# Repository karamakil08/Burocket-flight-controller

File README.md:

# Burocket Flight Controller

This is a flight controller built around the STM32F405 MCU for model rocket applications designed to perform altitude, gyro, and acceleration measurements, fire pyrotechnics, and save flight data safely.

## Component Selection

The components selected for this project were chosen according to various measures:
* Application requirement
* Ease of supply
* Price
* Performance
* Footprint area

## Hardware Subsystems

Detailed documentation for each subsystem can be found below:

* [MCU](docs/MCU.md)
* [Sensors](docs/Sensors.md)
* [POWER](docs/POWER.md)
* [Relays](docs/Relays.md)
* [LoRa](docs/LoRa.md)
* [USB-C](docs/USB-C.md)
* [Flash Memory](docs/Flash_memory.md)
* [SD-Card](docs/SD-card.md)

## Pin Distribution & Firmware

You can find the STMCubeMX pin distribution and firmware source files here:
* 🔗 [Firmware Directory](https://github.com/karamakil08/Burocket-flight-controller/tree/main/Firmware)

## Documentation & Resources

* 🔗 [Datasheets](https://github.com/karamakil08/Burocket-flight-controller/tree/main/docs/Datasheets)
* 🔗 [Application Notes](https://github.com/karamakil08/Burocket-flight-controller/tree/main/docs/App%20notes)
* 🔗 [Additional Useful Resources](https://github.com/karamakil08/Burocket-flight-controller/blob/main/docs/App%20notes/Links%20to%20additional%20resources%20I%20found%20useful.md)

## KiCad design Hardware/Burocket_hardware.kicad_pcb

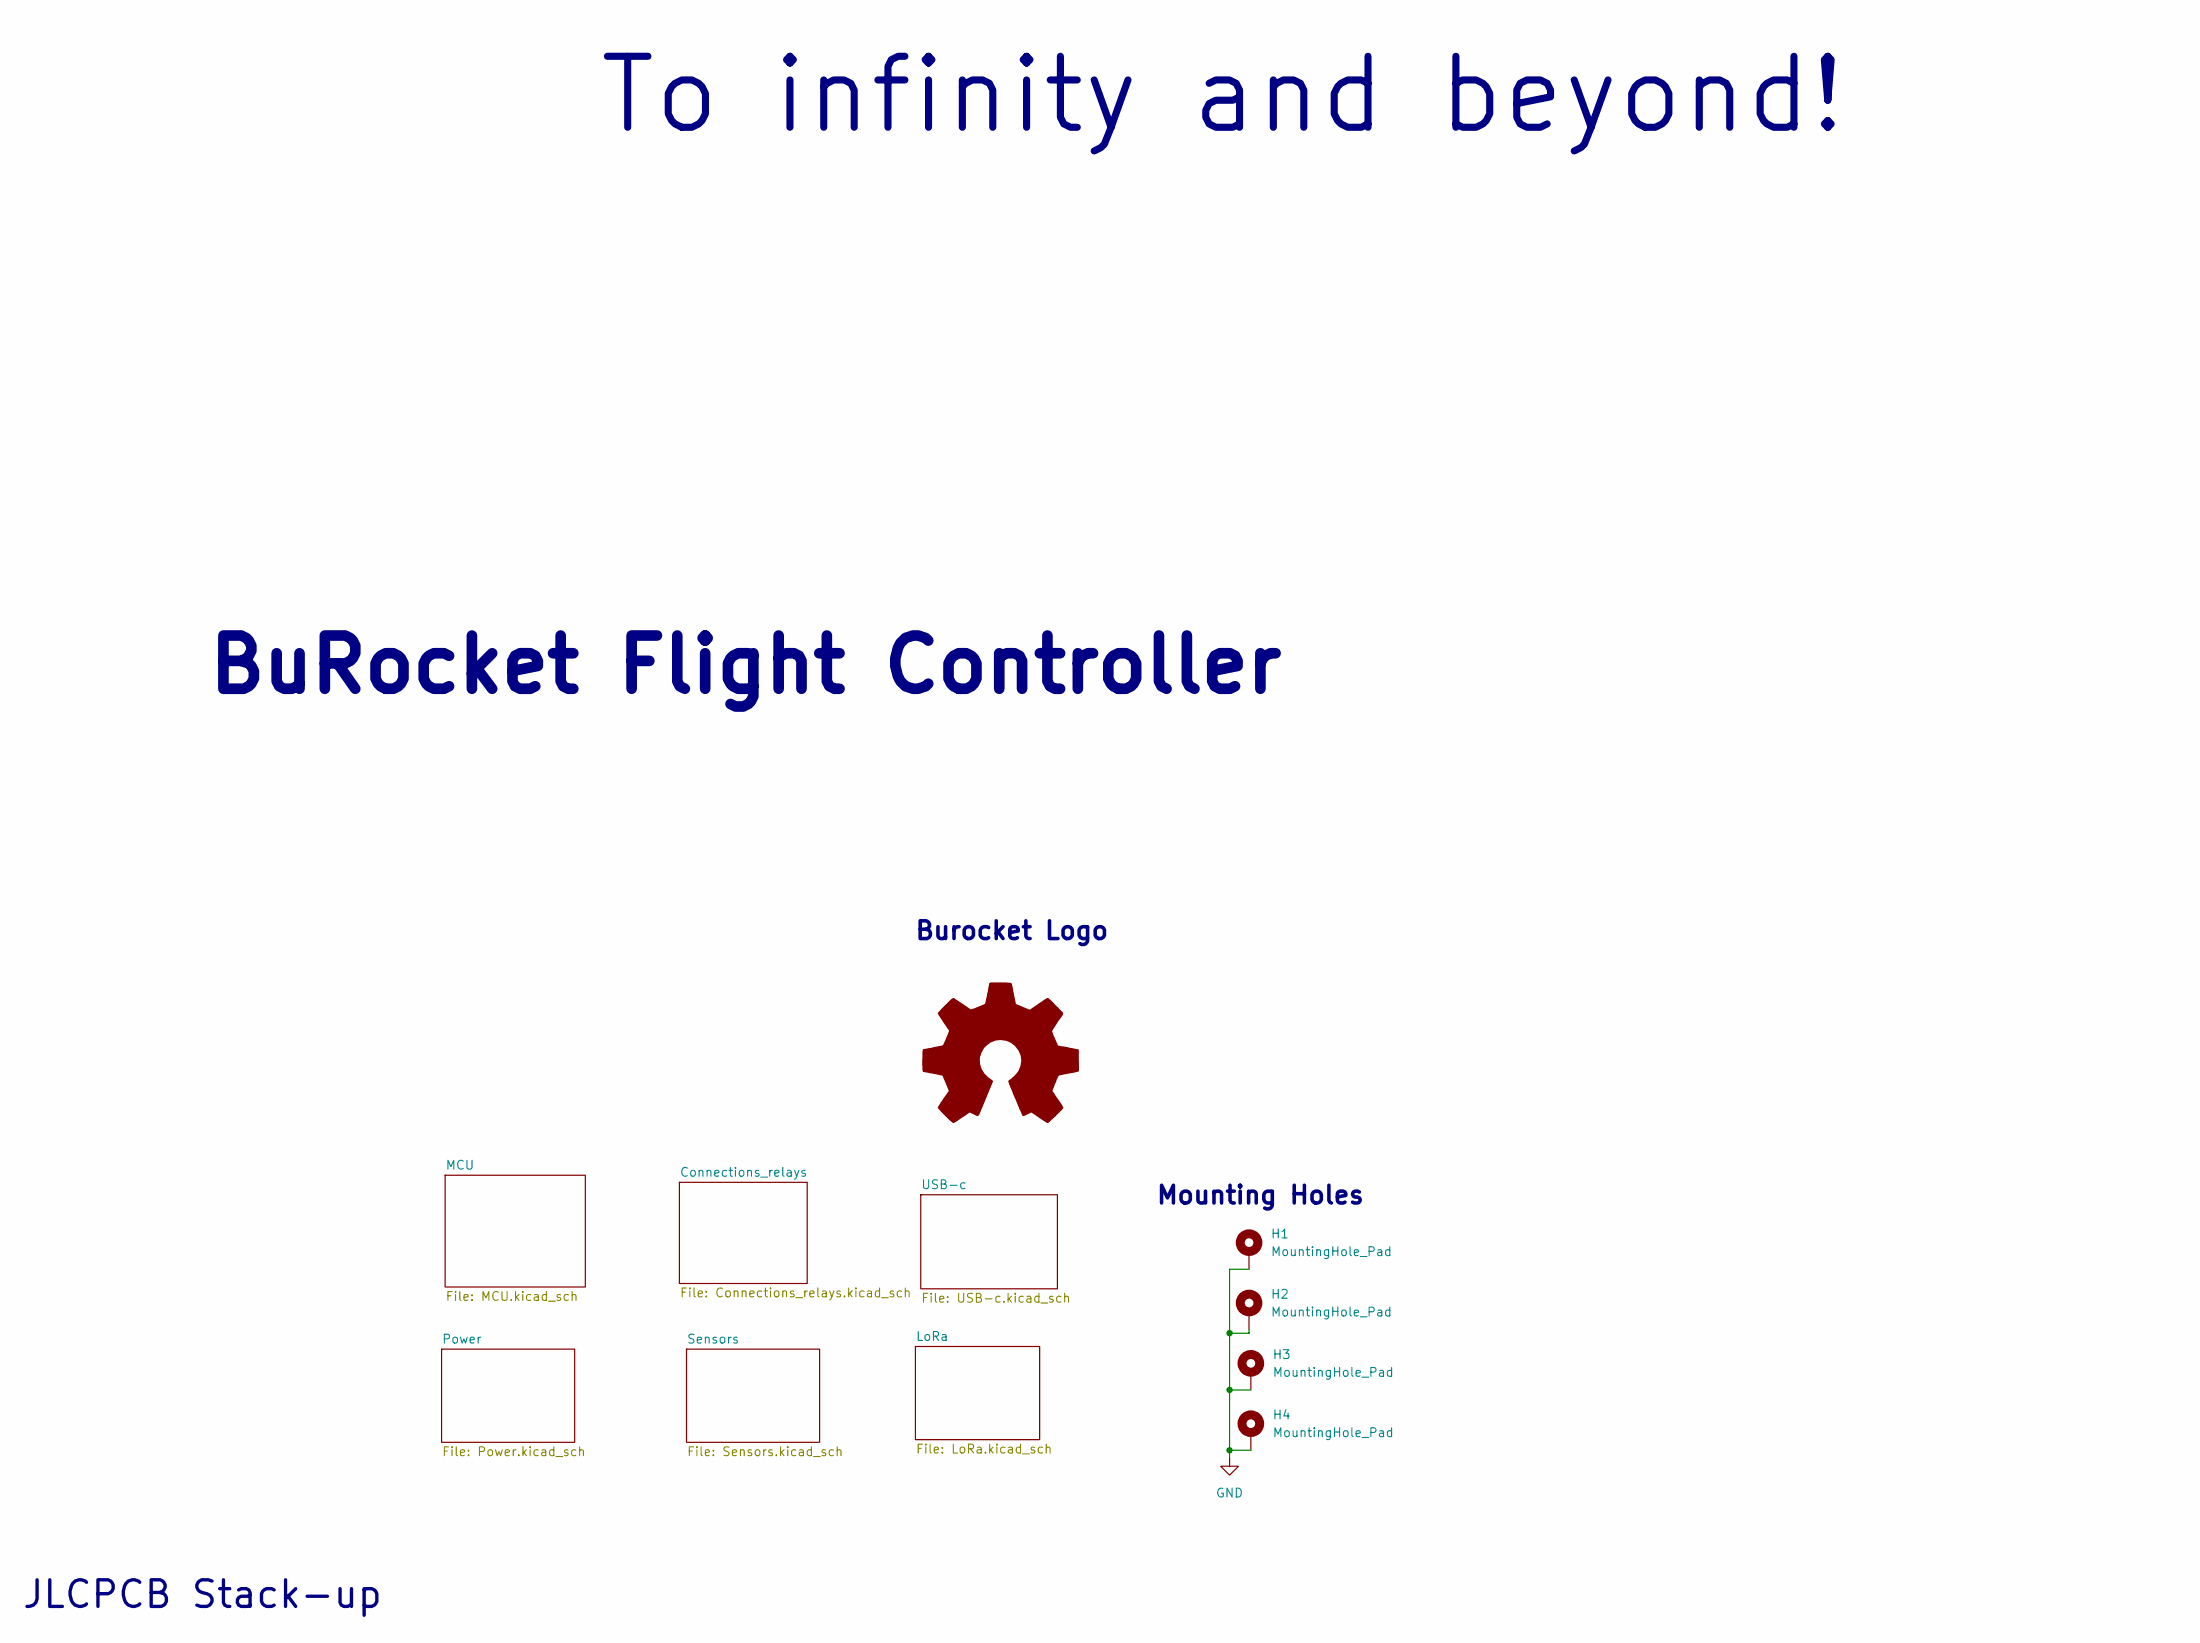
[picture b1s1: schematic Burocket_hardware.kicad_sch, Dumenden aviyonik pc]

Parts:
H1, H2, H3, H4: MountingHole_Pad; MountingHole_2.2mm_M2_Pad_Via
Logo1: Burocket Logo

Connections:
GND: H1.1 (1_1), H2.1 (1_1), H3.1 (1_1), H4.1 (1_1); also elsewhere on the board

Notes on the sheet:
Burocket Logo
BuRocket Flight Controller
JLCPCB Stack-up
Mounting Holes
To infinity and beyond!

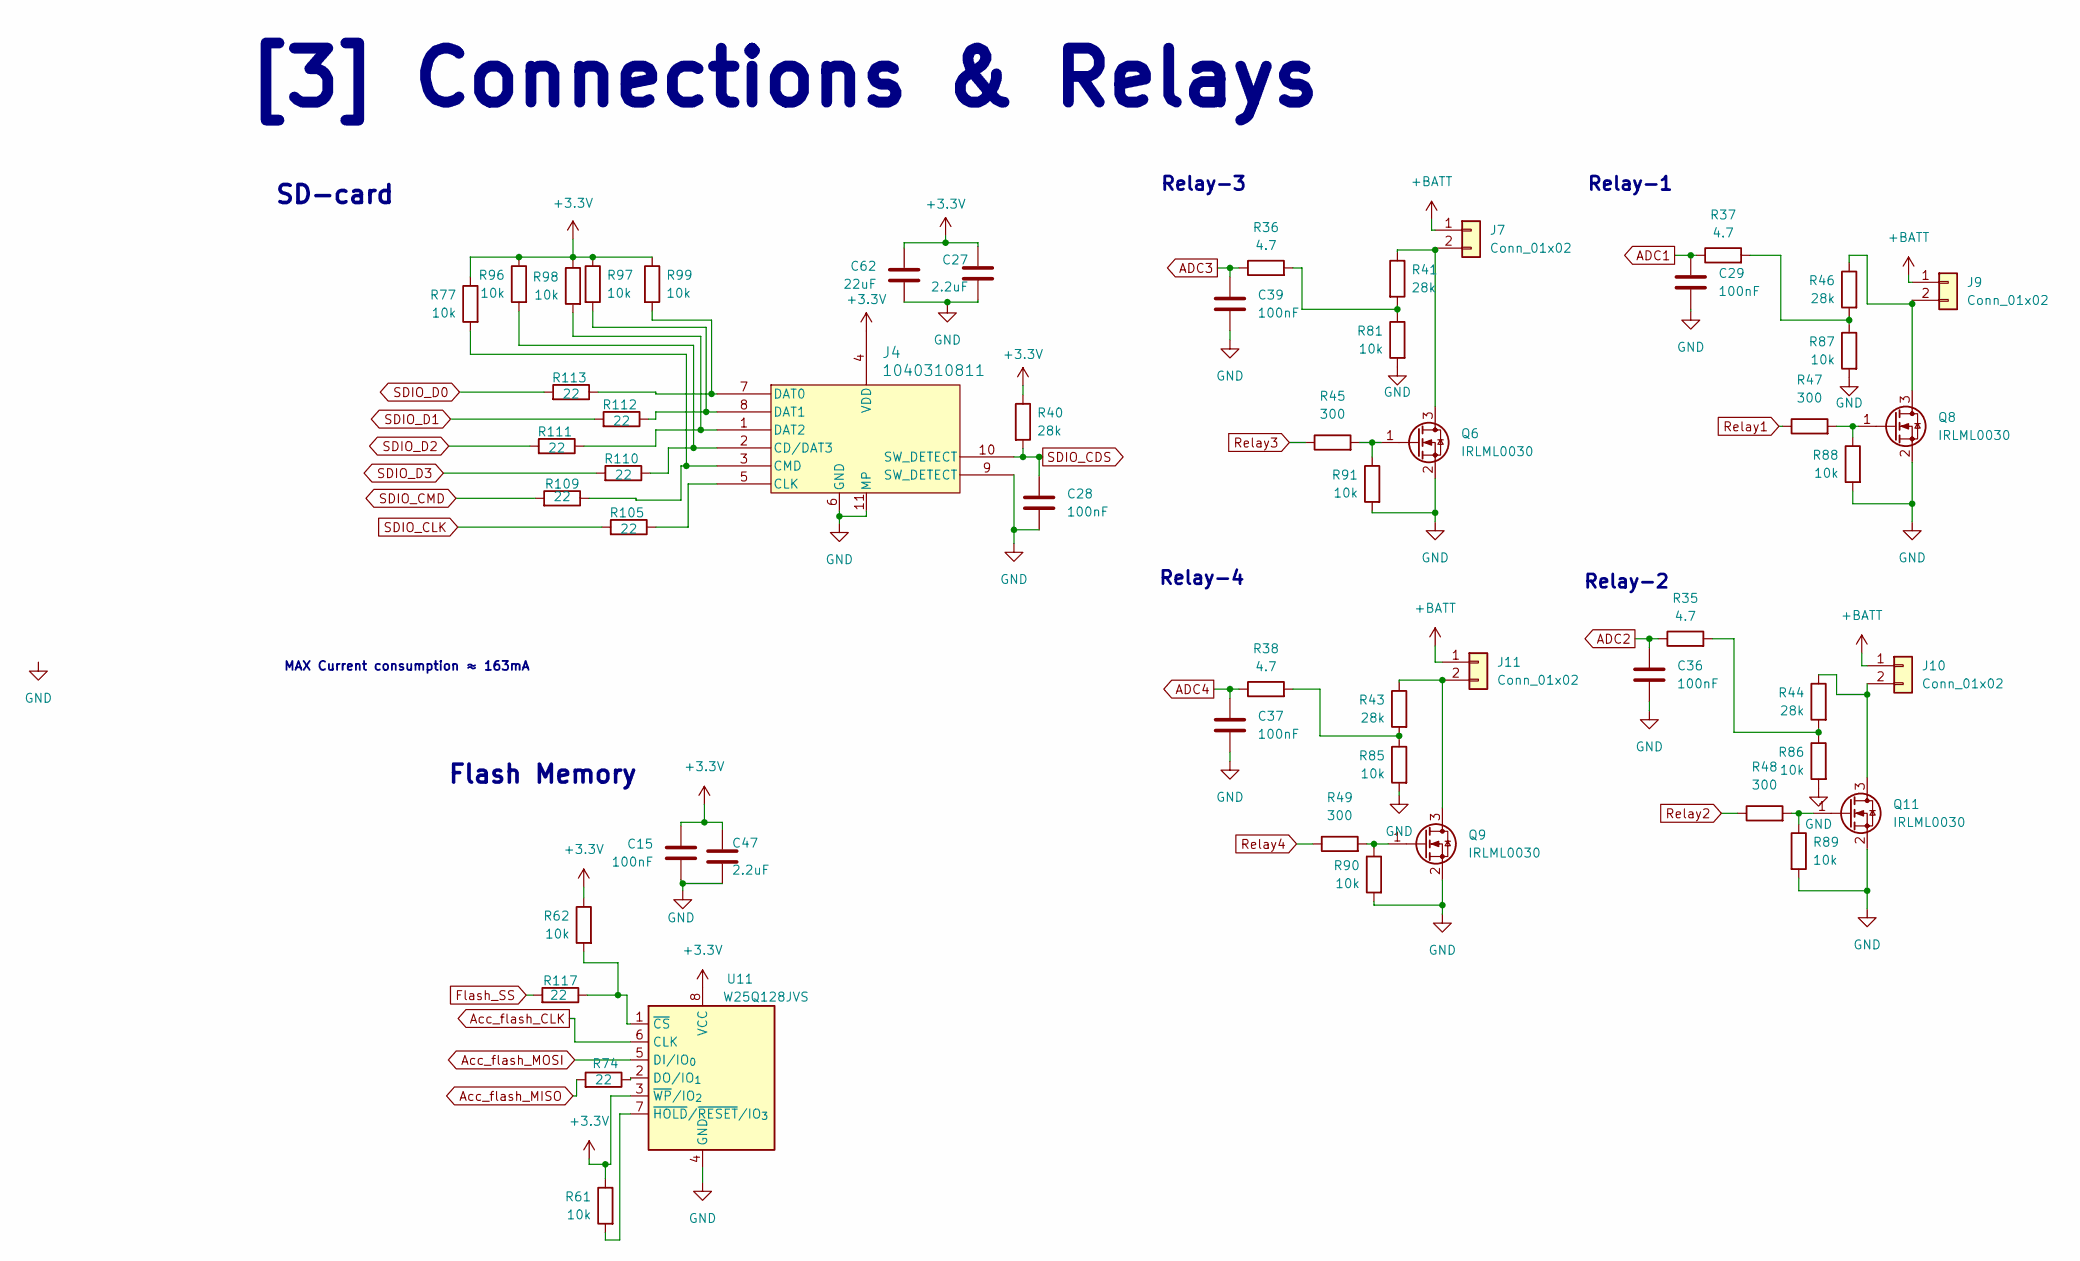
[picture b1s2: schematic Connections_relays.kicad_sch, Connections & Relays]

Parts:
C15, C28, C29, C36, C37, C39: 100nF; C_0603_1608Metric; Part Number CL10B104KO8WPNC
C27, C47: 2.2uF; C_0603_1608Metric; Part Number CL10B225KP8NNNC
C62: 22uF; C_0805_2012Metric; Part Number CL21A226KOQNNNE
J4: 1040310811; 104031-0811_MOL
J7, J9, J10, J11: Conn_01x02; E-match_Solder
Q6, Q8, Q9, Q11: IRLML0030; SOT-23
R35, R36, R37, R38: 4.7; R_0603_1608Metric; Part Number CQ03SAF470KT5E
R40, R41, R43, R44, R46: 28k; R_0603_1608Metric; Part Number MCT06030C2802FP500
R45, R47, R48, R49: 300; R_0603_1608Metric; Part Number ERJ3EKF3000V
R61, R62, R77, R88, R89, R90, R91, R96, R97, R98, R99: 10k; R_0603_1608Metric; Part Number CRT03J7E1002
R74, R105, R109, R110, R111, R112, R113, R117: 22; R_0603_1608Metric; Part Number CQ03SAJ0220T5E
R81, R85, R86, R87: 10k; R_0603_1608Metric; Part Number TC0350B1002T5F
U11: W25Q128JVS; SOIC-8_5.3x5.3mm_P1.27mm; Part Number W25Q128JVSIQ

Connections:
+3.3V: C15.1, C27.1, C47.1, C62.1, J4.4 (VDD), R40.1, R61.1, R62.1, R77.1, R96.1, R97.1, R98.1, R99.1, U11.3 (~WP/IO_{2}), U11.8 (VCC); also elsewhere on the board
+BATT: J7.1, J9.1, J10.1, J11.1; also elsewhere on the board
ADC1: C29.1, R37.1; also elsewhere on the board
ADC2: C36.1, R35.1; also elsewhere on the board
ADC3: C39.1, R36.1; also elsewhere on the board
ADC4: C37.1, R38.1; also elsewhere on the board
Acc_flash_CLK: U11.6 (CLK); also elsewhere on the board
Acc_flash_MOSI: U11.5 (DI/IO_{0}); also elsewhere on the board
Flash_SS: R117.2; also elsewhere on the board
GND: C15.2, C27.2, C28.2, C29.2, C36.2, C37.2, C39.2, C47.2, C62.2, J4.6 (GND), J4.9 (SW_DETECT), J4.11 (MP), J4.12 (MP), J4.13 (MP), J4.14 (MP), Q6.2 (S), Q8.2 (S), Q9.2 (S), Q11.2 (S), R81.2, R85.2, R86.2, R87.2, R88.2, R89.2, R90.2, R91.2, U11.4 (GND); also elsewhere on the board
unnamed: J4.2 (CD/DAT3), R96.2, R110.1
unnamed: J4.5 (CLK), R105.1
unnamed: J4.3 (CMD), R77.2, R109.1
unnamed: J4.7 (DAT0), R99.2, R113.1
unnamed: J4.8 (DAT1), R97.2, R112.1
unnamed: J4.1 (DAT2), R98.2, R111.1
unnamed: J7.2, Q6.3 (D), R41.1
unnamed: J9.2, Q8.3 (D), R46.1
unnamed: J10.2, Q11.3 (D), R44.1
unnamed: J11.2, Q9.3 (D), R43.1
unnamed: Q6.1 (G), R45.2, R91.1
unnamed: Q8.1 (G), R47.2, R88.1
unnamed: Q9.1 (G), R49.2, R90.1
unnamed: Q11.1 (G), R48.2, R89.1
unnamed: R35.2, R44.2, R86.1
unnamed: R36.2, R41.2, R81.1
unnamed: R37.2, R46.2, R87.1
unnamed: R38.2, R43.2, R85.1
unnamed: R74.1, U11.2 (DO/IO_{1})
unnamed: R62.2, R117.1, U11.1 (~CS)
unnamed: R61.2, U11.7 (~HOLD/~RESET/IO_{3})
Relay1: R47.1; also elsewhere on the board
Relay2: R48.1; also elsewhere on the board
Relay3: R45.1; also elsewhere on the board
Relay4: R49.1; also elsewhere on the board
SDIO_CDS: C28.1, J4.10 (SW_DETECT), R40.2; also elsewhere on the board
SDIO_CLK: R105.2; also elsewhere on the board
SDIO_CMD: R109.2; also elsewhere on the board
SDIO_D0: R113.2; also elsewhere on the board
SDIO_D1: R112.2; also elsewhere on the board
SDIO_D2: R111.2; also elsewhere on the board
SDIO_D3: R110.2; also elsewhere on the board

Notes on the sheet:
Relay-1
[3] Connections & Relays
Relay-3
MAX Current consumption ≈ 163mA
Flash Memory
Relay-4
SD-card
Relay-2

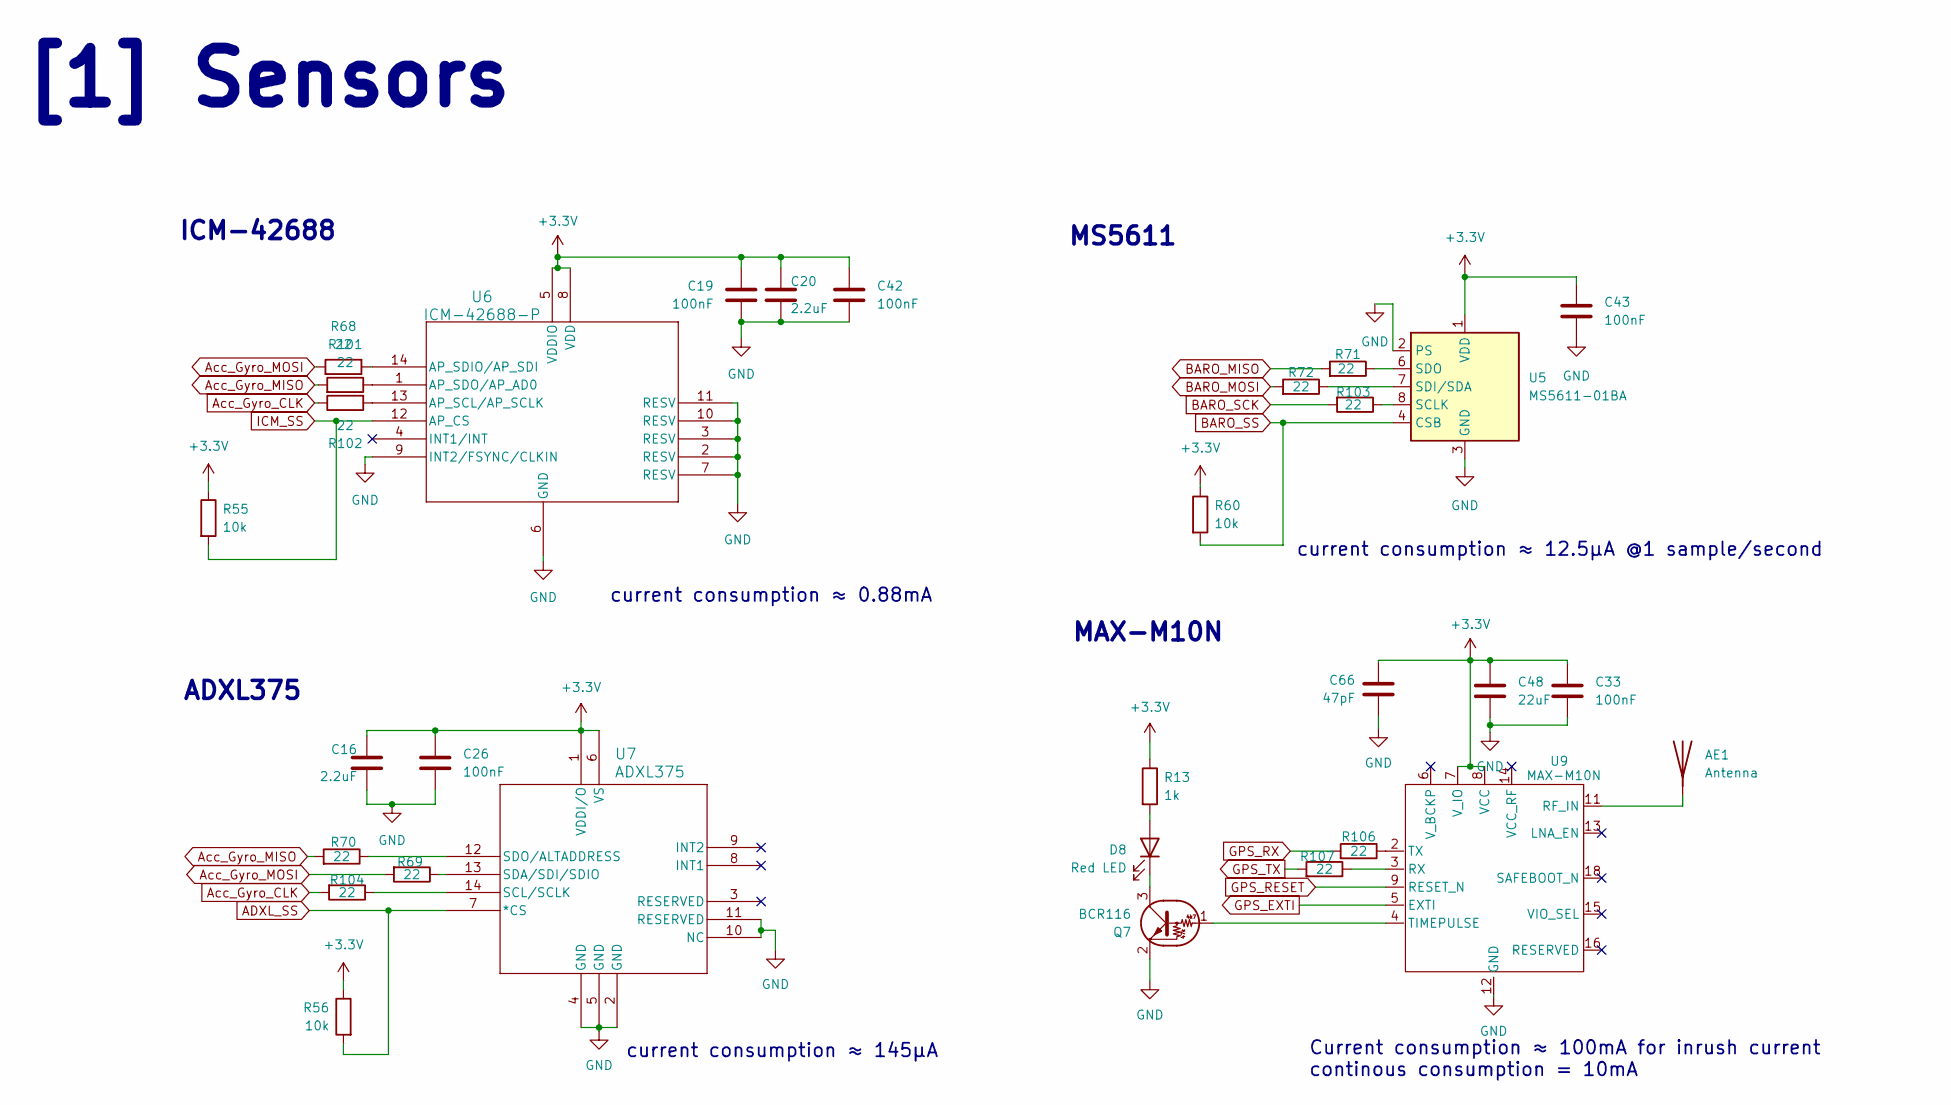
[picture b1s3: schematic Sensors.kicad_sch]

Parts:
AE1: Antenna; SMA_Amphenol_132134-10_Vertical
C16, C20: 2.2uF; C_0603_1608Metric; Part Number CL10B225KP8NNNC
C19, C26, C33, C42, C43: 100nF; C_0603_1608Metric; Part Number CL10B104KO8WPNC
C48: 22uF; C_0805_2012Metric; Part Number CL21A226KOQNNNE
C66: 47pF; C_0603_1608Metric; Part Number CL10C470JB81PNC
D8: Red LED; C_0603_1608Metric; Part Number 27-21/R6C-AP1Q2B/3C
Q7: BCR116; SOT-23-3; Part Number BCR116E6327HTSA1
R13: 1k; R_0603_1608Metric; Part Number CRCW06031K00JNTABC
R55, R56, R60: 10k; R_0603_1608Metric; Part Number CRT03J7E1002
R68, R69, R70, R71, R72, R101, R102, R103, R104, R106, R107: 22; R_0603_1608Metric; Part Number CQ03SAJ0220T5E
U5: MS5611-01BA; LGA-8_3x5mm_P1.25mm; Part Number MS561101BA03-50
U6: ICM-42688-P; LGA14_2P5X3X0P91_TDK; Part Number ICM-42688-P
U7: ADXL375; LGA_CC-14-1_ADI-L; Part Number ADXL375BCCZ-RL7
U9: MAX-M10N; ublox_MAX; Part Number MAX-M10N-00B

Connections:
+3.3V: C16.1, C19.1, C20.1, C26.1, C33.1, C42.1, C43.1, C48.1, C66.1, R13.1, R55.1, R56.1, R60.1, U5.1 (VDD), U6.5 (VDDIO), U6.8 (VDD), U7.1 (VDDI/O), U7.6 (VS), U9.7 (V_IO), U9.8 (VCC); also elsewhere on the board
/Sensors/Connector_feed: AE1.1, U9.11 (RF_IN); also elsewhere on the board
Acc_flash_CLK: R104.1, U7.14 (SCL/SCLK); also elsewhere on the board
Acc_flash_MOSI: R69.1, U7.13 (SDA/SDI/SDIO); also elsewhere on the board
BARO_icm_MOSI: R68.1, R72.1, U5.7 (SDI/SDA), U6.14 (AP_SDIO/AP_SDI); also elsewhere on the board
GND: C16.2, C19.2, C20.2, C26.2, C33.2, C42.2, C43.2, C48.2, C66.2, Q7.2 (E), U5.2 (PS), U5.3 (GND), U6.2 (RESV), U6.3 (RESV), U6.6 (GND), U6.7 (RESV), U6.9 (INT2/FSYNC/CLKIN), U6.10 (RESV), U6.11 (RESV), U7.2 (GND), U7.4 (GND), U7.5 (GND), U7.10 (NC), U7.11 (RESERVED), U9.1 (GND), U9.10 (GND), U9.12 (GND); also elsewhere on the board
GPS_RX: R106.2; also elsewhere on the board
GPS_TX: R107.2; also elsewhere on the board
unnamed: D8.2 (A), R13.2
unnamed: D8.1 (K), Q7.3 (C)
unnamed: Q7.1 (B), U9.4 (TIMEPULSE)
unnamed: R68.2, R69.2
unnamed 78: R60.2, U5.4 (CSB), U5.5 (CSB); also elsewhere on the board
unnamed: R71.1, U5.6 (SDO)
unnamed: R101.1, U6.1 (AP_SDO/AP_AD0)
unnamed 86: R56.2, U7.7 (*CS); also elsewhere on the board
unnamed: R70.1, U7.12 (SDO/ALTADDRESS)
unnamed 93: U9.5 (EXTI); also elsewhere on the board
unnamed 94: U9.9 (RESET_N); also elsewhere on the board
unnamed: R107.1, U9.3 (RX)
unnamed: R106.1, U9.2 (TX)

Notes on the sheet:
current consumption ≈ 12.5µA @1 sample/second
ICM-42688
[1] Sensors
MAX-M10N
current consumption ≈ 145µA
current consumption ≈ 0.88mA
MS5611
Current consumption ≈ 100mA for inrush current continous consumption = 10mA
ADXL375

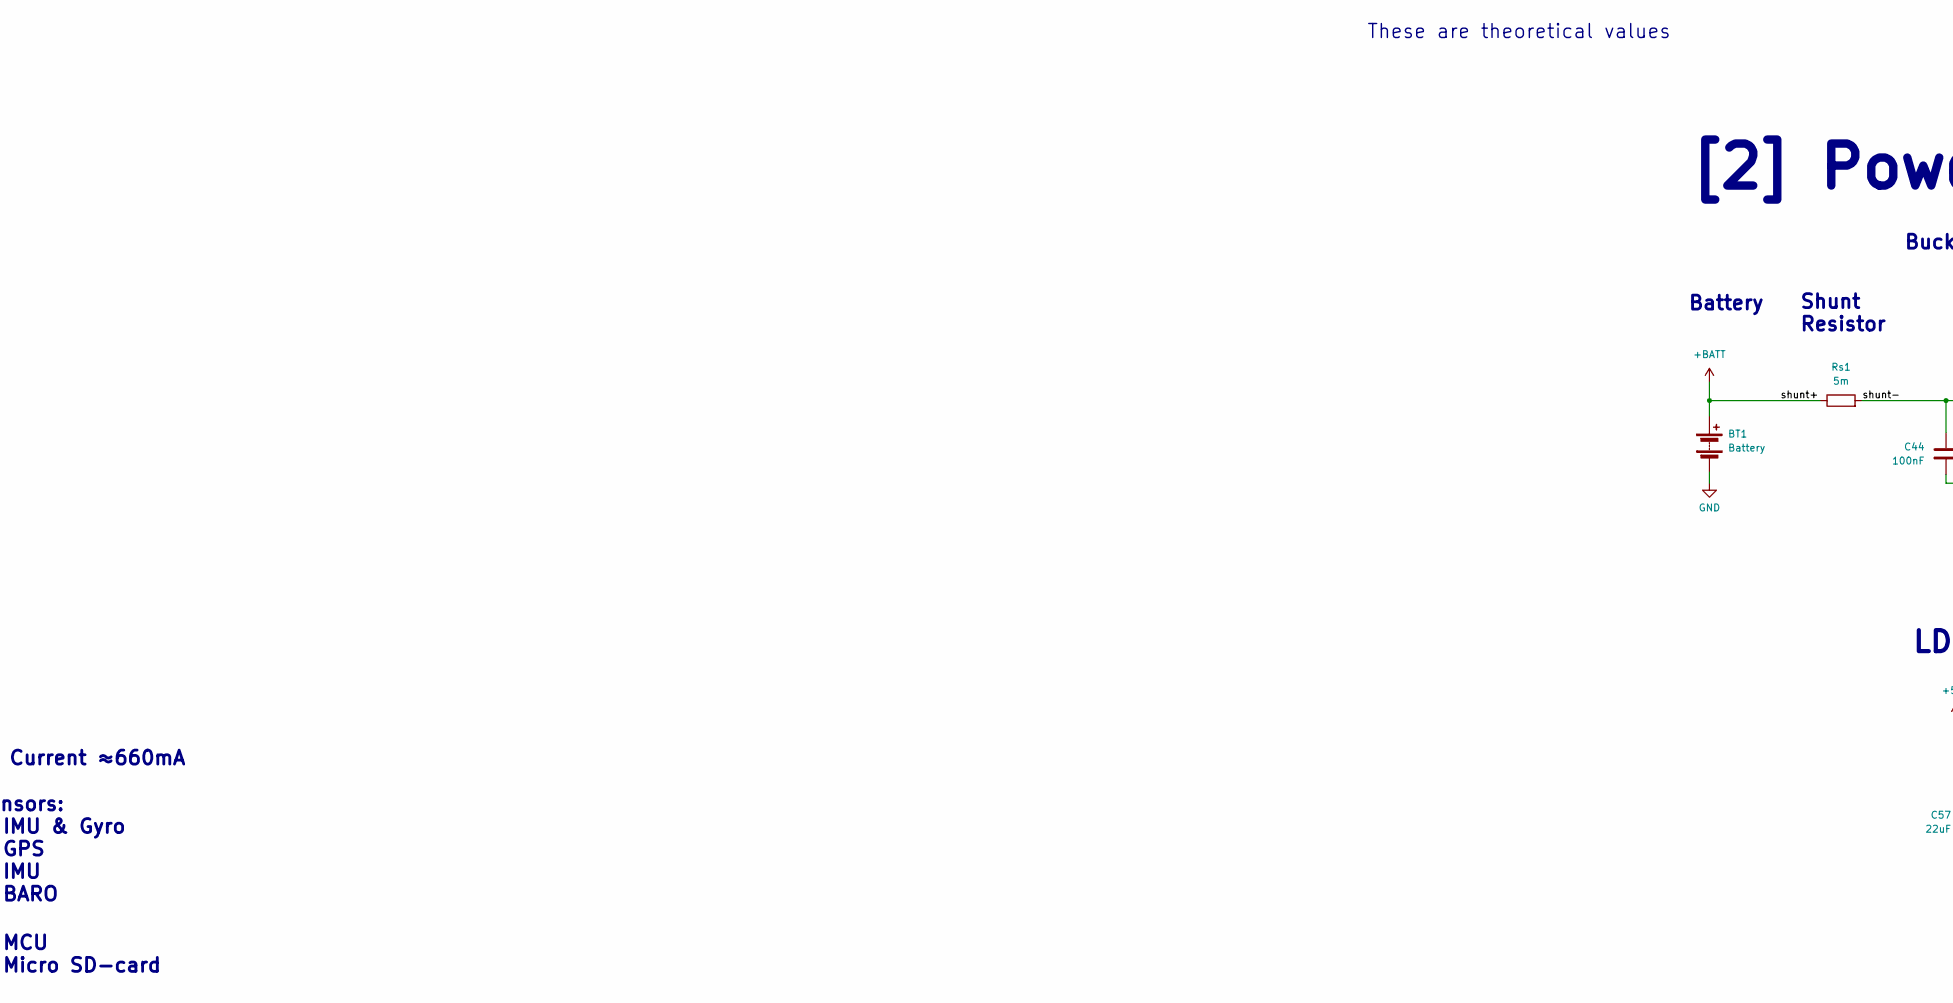
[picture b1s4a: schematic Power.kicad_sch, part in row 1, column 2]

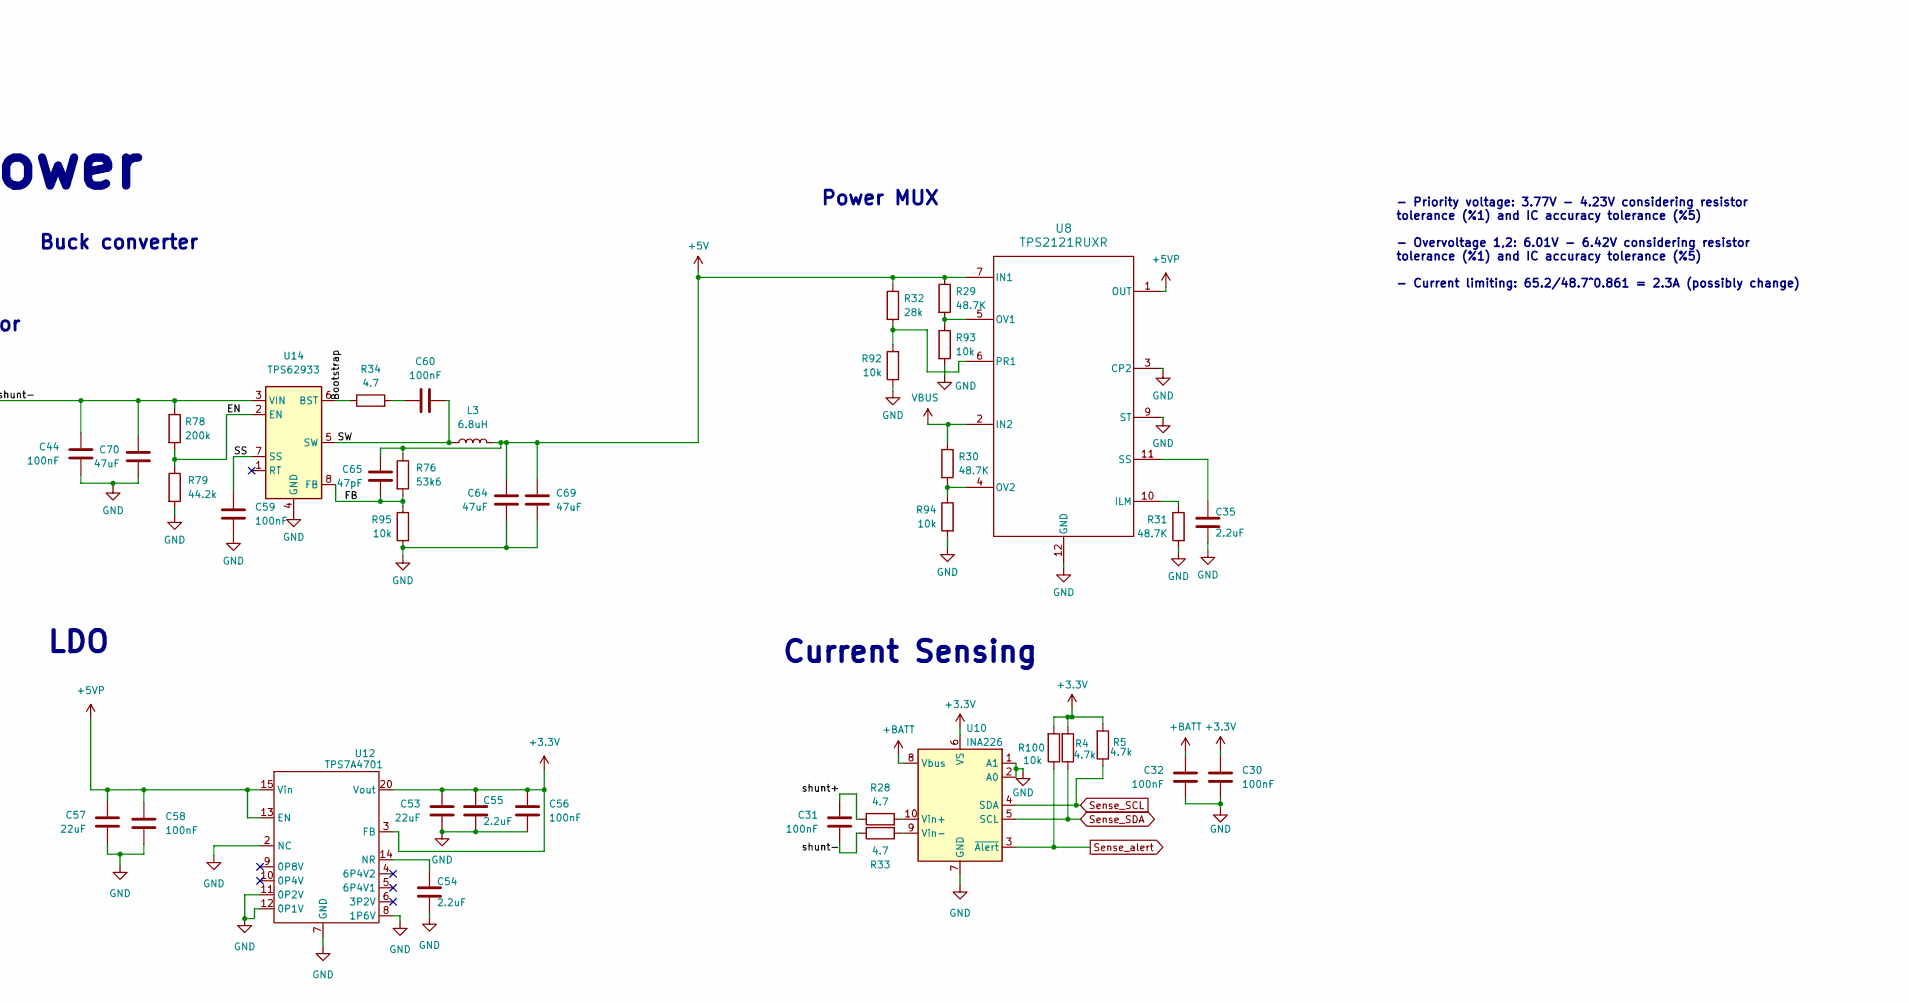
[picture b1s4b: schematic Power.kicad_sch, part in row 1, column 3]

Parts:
BT1: Battery; AMASS_XT60-M_1x02_P7.20mm_Vertical; Part Number XT60
C30, C31, C32, C44, C56, C58, C59, C60: 100nF; C_0603_1608Metric; Part Number CL10B104KO8WPNC
C35, C54, C55: 2.2uF; C_0603_1608Metric; Part Number CL10B225KP8NNNC
C53, C57: 22uF; C_0805_2012Metric; Part Number CL21A226KOQNNNE
C64, C69, C70: 47uF; C_1210_3225Metric; Part Number CL32A476KOJNNNE
C65: 47pF; C_0603_1608Metric; Part Number CL10C470JB81PNC
L3: 6.8uH; L_Wuerth_XHMI-6060; Part Number 74439346068
R4, R5: 4.7k; R_0603_1608Metric; Part Number CQ03SAJ0472T5E
R28, R33, R34: 4.7; R_0603_1608Metric; Part Number CQ03SAF470KT5E
R29, R30, R31: 48.7K; R_0603_1608Metric; Part Number 0603SAF4872T5E
R32: 28k; R_0603_1608Metric; Part Number MCT06030C2802FP500
R76: 53k6; R_0603_1608Metric; Part Number RT0603BRD0753K6L
R78: 200k; R_0603_1608Metric; Part Number TC0325B2003T5C
R79: 44.2k; R_0603_1608Metric; Part Number RT0603FRE0744K2L
R92, R93, R94, R95: 10k; R_0603_1608Metric; Part Number TC0350B1002T5F
R100: 10k; R_0603_1608Metric; Part Number CRT03J7E1002
Rs1: 5m; R_1206_3216Metric; Part Number WSLP12065L000FEA
U8: TPS2121RUXR; RUX0012A; Part Number TPS2121RUXR
U10: INA226; TSSOP-10_3x3mm_P0.5mm; Part Number INA226AIDGSR
U12: TPS7A4701; Texas_RGW0020A_VQFN-20-1EP_5x5mm_P0.65mm_EP3.15x3.15mm; Part Number TPS7A4701
U14: TPS62933; SOT-583-8

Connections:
+3.3V: C30.1, C53.1, C55.1, C56.1, R4.2, R5.2, R100.2, U10.6 (VS), U12.1 (Vout), U12.3 (FB), U12.20 (Vout); also elsewhere on the board
+5V: C64.1, C65.1, C69.1, L3.2, R29.1, R32.1, R76.1, U8.7 (IN1); also elsewhere on the board
+5VP: C57.1, C58.1, U8.1 (OUT), U8.8 (OUT), U12.13 (EN), U12.15 (Vin), U12.16 (Vin); also elsewhere on the board
+BATT: BT1.1 (+), C31.1, C32.1, R28.1, Rs1.1, U10.8 (Vbus); also elsewhere on the board
/Power/Bootstrap: R34.1, U14.6 (BST)
/Power/EN: R78.2, R79.1, U14.2 (EN)
/Power/FB: C65.2, R76.2, R95.1, U14.8 (FB)
/Power/SS: C59.1, U14.7 (SS)
/Power/SW: C60.2, L3.1, U14.5 (SW)
/Power/shunt-: C31.2, C44.1, C70.1, R33.1, R78.1, Rs1.2, U14.3 (VIN)
GND: BT1.2 (-), C30.2, C32.2, C35.2, C44.2, C53.2, C54.2, C55.2, C56.2, C57.2, C58.2, C59.2, C64.2, C69.2, C70.2, R31.2, R79.2, R92.2, R93.2, R94.2, R95.2, U8.3 (CP2), U8.9 (ST), U8.12 (GND), U10.1 (A1), U10.2 (A0), U10.7 (GND), U12.2 (NC), U12.7 (GND), U12.8 (1P6V), U12.11 (0P2V), U12.12 (0P1V), U12.17 (NC), U12.18 (NC), U12.19 (NC), U12.21 (PAD), U14.4 (GND); also elsewhere on the board
unnamed: C60.1, R34.2
unnamed: R31.1, U8.10 (ILM)
unnamed: R29.2, R93.1, U8.5 (OV1)
unnamed: R30.2, R94.1, U8.4 (OV2)
unnamed: R32.2, R92.1, U8.6 (PR1)
unnamed: C35.1, U8.11 (SS)
unnamed: R28.2, U10.10 (Vin+)
unnamed: R33.2, U10.9 (Vin-)
unnamed: C54.1, U12.14 (NR)
Sense_SCL: R5.1, U10.4 (SDA); also elsewhere on the board
Sense_SDA: R4.1, U10.5 (SCL); also elsewhere on the board
Sense_alert: R100.1, U10.3 (~Alert); also elsewhere on the board
VBUS: R30.1, U8.2 (IN2); also elsewhere on the board

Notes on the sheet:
Power MUX
Battery
LDO
These are theoretical values
- MCU - Micro SD-card
MAX Current ≈660mA
3.3V
[2] Power
----->
Buck converter
Current Sensing
Shunt Resistor
Sensors: - IMU & Gyro - GPS - IMU - BARO
USB-c ------>
- Priority voltage: 3.77V - 4.23V considering resistor tolerance (%1) and IC accuracy tolerance (%5) - Overvoltage 1,2: 6.01V - 6.42V considering resistor tolerance (%1) and IC accuracy tolerance (%5) - Current limiting: 65.2/48.7^0.861 = 2.3A (possibly change)
2S 6-8.4V
Buck converter ----->
Power input ---->
Power MUX
